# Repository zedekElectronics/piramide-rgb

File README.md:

# piramide-rgb

Lámpara Led RGB de sobremesa o escritorio.

Utiliza un LED RGB High Power tipo estrella de 3W.

Control y mezcla manual de colores mediante potenciómetros dedicados:
 - Rojo, Verde y Azul.

Base, parte superior y perillas realizadas en impresión 3D con filamento PLA.

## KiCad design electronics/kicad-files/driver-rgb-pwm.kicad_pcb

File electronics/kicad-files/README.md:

Archivos de KiCad:
- Esquemático.
- PCB.

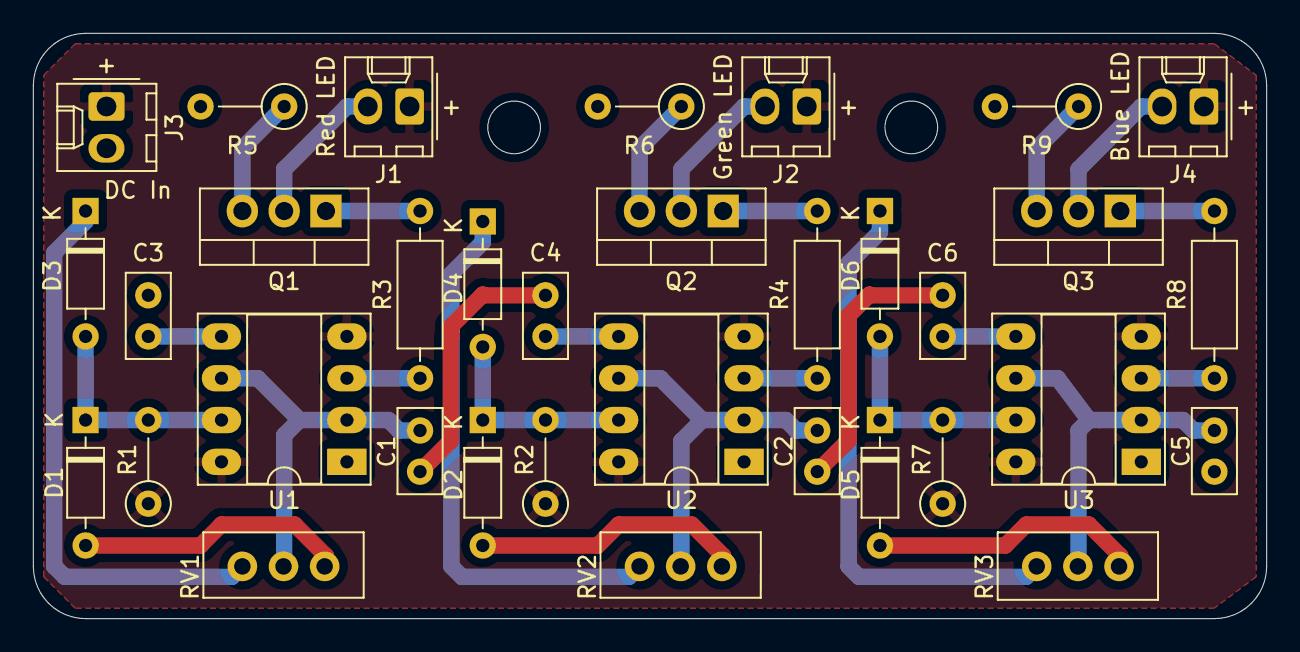
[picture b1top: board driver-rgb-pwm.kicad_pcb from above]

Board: 2 copper layers, 74.9 x 35.6 mm, 34 parts (0 on the bottom side), 29 nets.

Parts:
C1, C2, C3, C4, C5, C6: 10nF; C_Disc_D5.0mm_W2.5mm_P2.50mm
D1, D2, D3, D4, D5, D6: 1N4148; D_DO-35_SOD27_P7.62mm_Horizontal
J1: Red Led; Molex_KK-254_AE-6410-02A_1x02_P2.54mm_Vertical
J2: Blue Led; Molex_KK-254_AE-6410-02A_1x02_P2.54mm_Vertical
J3: DC In; Molex_KK-254_AE-6410-02A_1x02_P2.54mm_Vertical
J4: Green Led; Molex_KK-254_AE-6410-02A_1x02_P2.54mm_Vertical
Q1, Q2, Q3: IRF540N; TO-220-3_Vertical
R1, R2, R7: 1k; R_Axial_DIN0207_L6.3mm_D2.5mm_P5.08mm_Vertical
R3, R4, R8: 10k; R_Axial_DIN0207_L6.3mm_D2.5mm_P10.16mm_Horizontal
R5: 5,6; R_Axial_DIN0207_L6.3mm_D2.5mm_P5.08mm_Vertical
R6, R9: 2,7; R_Axial_DIN0207_L6.3mm_D2.5mm_P5.08mm_Vertical
RV1, RV2, RV3: 10k; Potentiometer_Alps_RK09Y11_Single_Horizontal
U1, U2, U3: LM555; DIP-8_W7.62mm_Socket_LongPads

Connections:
GND: C1.2, C2.2, C3.2, C4.2, C5.2, C6.2, J3.2, R5.2, R6.2, R9.2, U1.1, U2.1, U3.1
unnamed: C1.1, RV1.2, U1.2, U1.6
unnamed: C2.1, RV2.2, U2.2, U2.6
unnamed: C3.1, U1.5
unnamed: C4.1, U2.5
unnamed: C5.1, RV3.2, U3.2, U3.6
unnamed: C6.1, U3.5
unnamed: D1.1, D3.2, R1.2, U1.7
unnamed: D1.2, RV1.3
unnamed: D2.1, D4.2, R2.2, U2.7
unnamed: D2.2, RV2.3
unnamed: D3.1, RV1.1
unnamed: D4.1, RV2.1
unnamed: D5.1, D6.2, R7.2, U3.7
unnamed: D5.2, RV3.3
unnamed: D6.1, RV3.1
unnamed: J1.2, Q1.2
unnamed: J2.2, Q2.2
unnamed: J4.2, Q3.2
unnamed: Q1.1, R3.1
unnamed: Q1.3, R5.1
unnamed: Q2.1, R4.1
unnamed: Q2.3, R6.1
unnamed: Q3.1, R8.1
unnamed: Q3.3, R9.1
unnamed: R3.2, U1.3
unnamed: R4.2, U2.3
unnamed: R8.2, U3.3
VCC: J1.1, J2.1, J3.1, J4.1, R1.1, R2.1, R7.1, U1.4, U1.8, U2.4, U2.8, U3.4, U3.8

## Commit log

2021-08-10 Breve descripción
2021-08-10 STL files base y piramide
